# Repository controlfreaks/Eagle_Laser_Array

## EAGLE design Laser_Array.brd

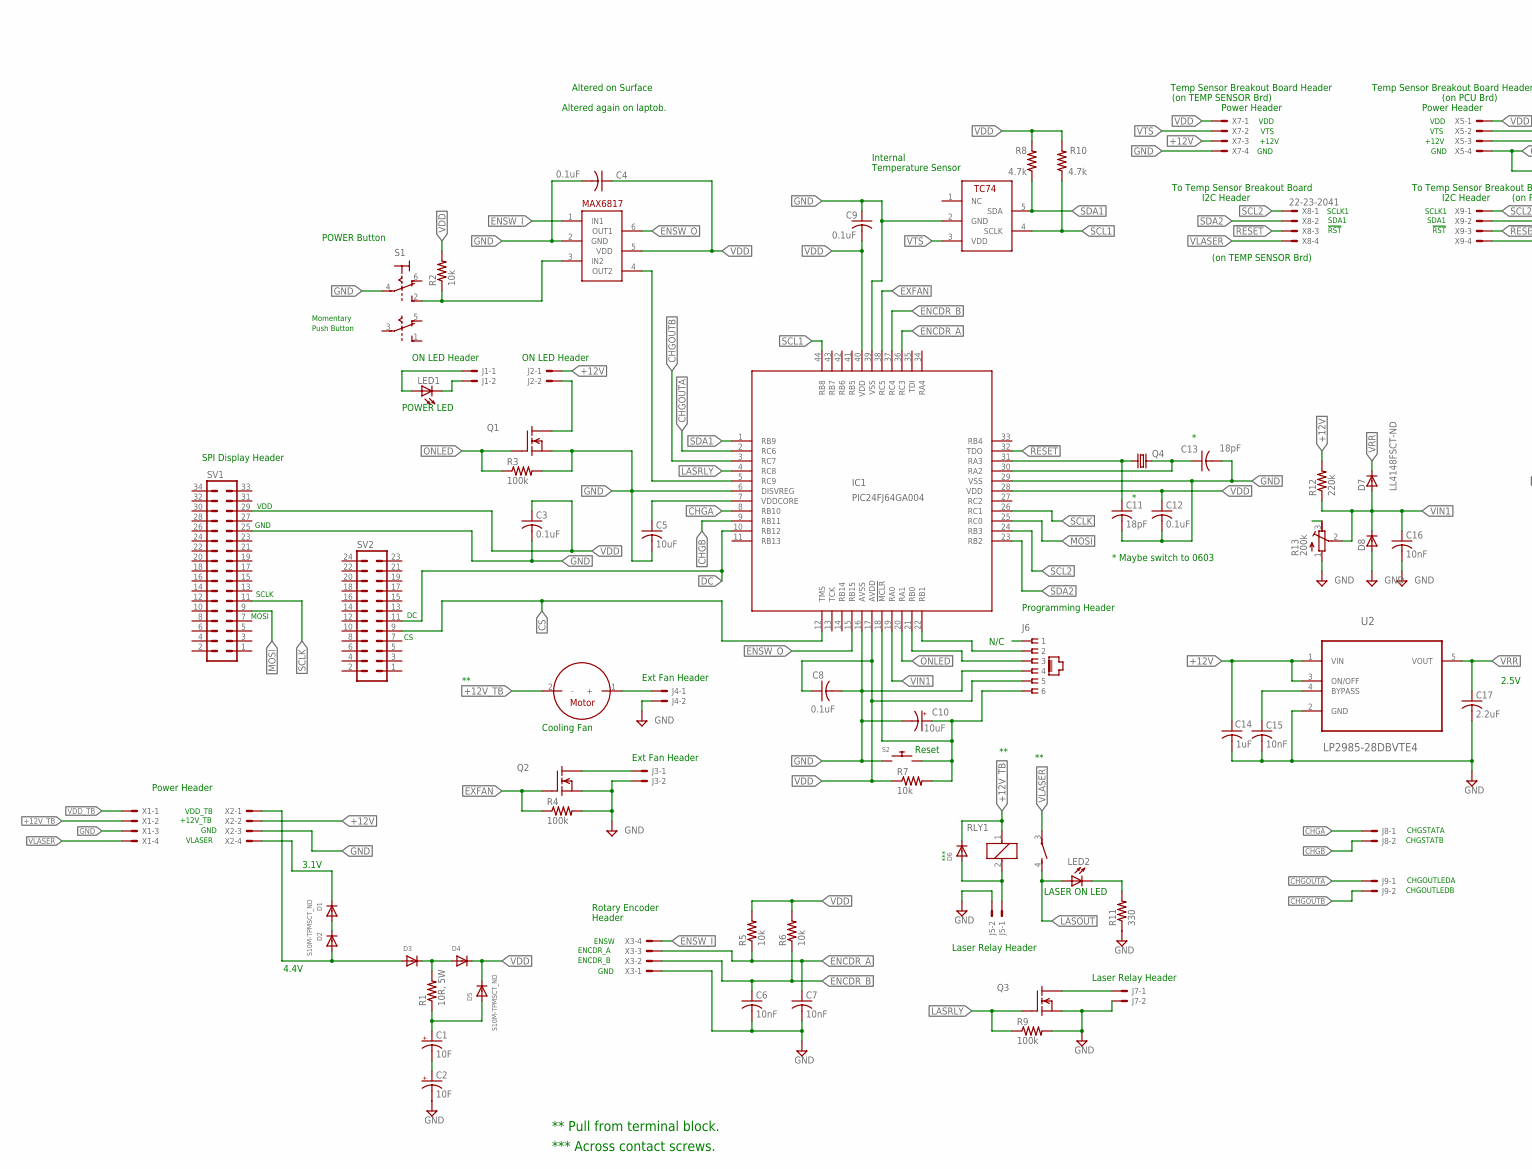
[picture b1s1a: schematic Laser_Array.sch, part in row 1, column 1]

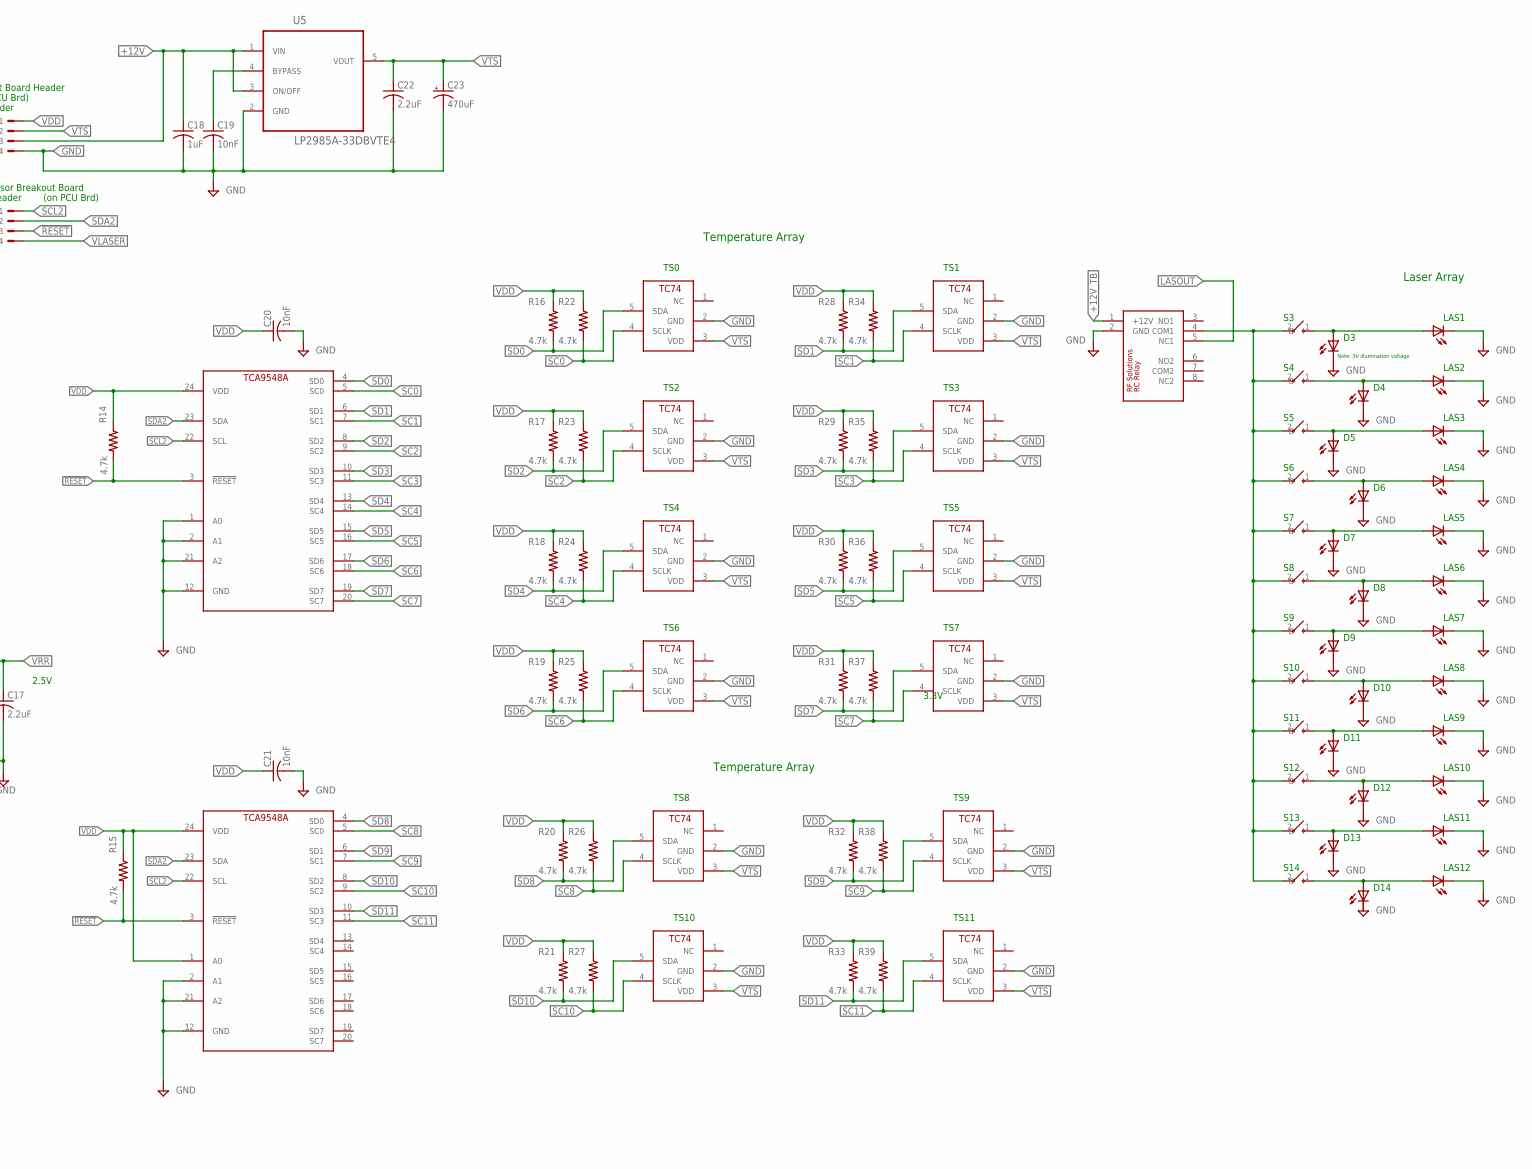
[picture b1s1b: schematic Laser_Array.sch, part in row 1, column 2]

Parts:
C1, C2: 10F; E5-10,5
C3, C4, C8, C9, C12: 0.1uF; C0805
C5: 10uF; C0805
C6, C7, C15, C16, C19, C20, C21: 10nF; C0805
C10: 10uF; CAP3X3
C11, C13: 18pF; C0805
C14, C18: 1uF; C0805
C17, C22: 2.2uF; C0805
C23: 470uF; PANASONIC_F
D1, D5: S10M-TPMSCT_ND; S10M-TPMSCT-ND
D2, D3, D4, D6: 641-1014-6-ND; SOD-123
D7, D8: LL4148FSCT-ND; SOD80
IC1: PIC24FJ64GA004; TQFP44
J1, J2, J3, J4, J5, J7, J8, J9: 22-23-2021
J6: RJ_25; RJ11-NO_SHIELD
LED1, LED2: LEDA5MM; LED5MM
LED3, LED4, LED5, LED6, LED7, LED8, LED9, LED10, LED11, LED12, LED13, LED14, LED15, LED16, LED17, LED18, LED19, LED20, LED21, LED22, LED23, LED24, LED25, LED26: LED3MM
M1: MOTOR; 22-23-2021
Q1, Q2, Q3: QS5U34CT-ND_MOSFET_N_CHANNEL; SOT23-5L
Q4: CRYSTALSM49; SM49
R1: 10R, 5W; RESISTOR5W
R2, R7: 10k; R0805
R3, R4, R9: 100k; R0805
R5, R6: 10k; M0805
R8, R10, R14, R15, R16, R17, R18, R19, R20, R21, R22, R23, R24, R25, R26, R27, R28, R29, R30, R31, R32, R33, R34, R35, R36, R37, R38, R39: 4.7k; M0805
R11: 330; R0805
R12: 220k; M0805
R13: 200k; RTRIM3224X
RLY1: RELAY_SPST
RLY2: RF_SOLUTIONS_RELAY
S1: DPDT_TOGGLE; 22-23-2061
S2: TACT_PB; PUSHBUTTON_SMD_SJ
S3, S4, S5, S6, S7, S8, S9, S10, S11, S12, S13, S14, S15: TC74; SOT23-5L
S16, S17, S18, S19, S20, S21, S22, S23, S24, S25, S26, S27: TOGGLE_SPST; 22-23-2021
SV1: MA17-2W
SV2: MA12-2
U1: MAX6817; SOT23-6
U2: LP2985-28DBVTE4; SOT95P280X145-5N
U3, U4: TCA9548A; TSSOP24
U5: LP2985A-33DBVTE4; SOT95P280X145-5N
X1, X2, X3, X5, X7, X8, X9: 22-23-2041

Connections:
!RESET: IC1.32 (TDO), R14.2, R15.2, U3.3 (!RESET), U4.3 (!RESET), X8.3, X9.3
+12V: C14.1, C18.1, J2.1, R12.2, U2.1 (VIN), U2.3 (ON/OFF), U5.1 (VIN), U5.3 (ON/OFF), X2.2, X5.3, X7.3
+12V_TB: D6.C, M1.2 (-), RLY1.1, RLY2.1 (+12V), X1.2
CHGA: IC1.8 (RB10), J8.1
CHGB: IC1.9 (RB11), J8.2
CHGOUTA: IC1.2 (RC6), J9.1
CHGOUTB: IC1.3 (RC7), J9.2
CS: IC1.12 (TMS), SV2.9
DC: IC1.10 (RB12), SV2.11
ENCDR_A: C7.1, IC1.36 (RC3), R5.1, X3.3
ENCDR_B: C6.1, IC1.37 (RC4), R6.1, X3.2
ENSW_I: U1.1 (IN1), X3.4
ENSW_O: IC1.15 (RB15), U1.6 (OUT1)
EXFAN: IC1.38 (RC5), Q2.1 (G), R4.1
GND: C2.-, C3.2, C4.2, C5.2, C6.2, C7.2, C8.2, C9.1, C10.-, C11.2, C12.2, C13.2, C14.2, C15.2, C16.2, C17.2, C18.2, C19.2, C20.2, C21.2, C22.2, C23.-, D8.2 (A), IC1.6 (DISVREG), IC1.16 (AVSS), IC1.29 (VSS), IC1.39 (VSS), J3.2, J4.2, J5.2, J6.4, J7.2, LED3.K (C), LED4.K (C), LED5.K (C), LED6.K (C), LED7.K (C), LED8.K (C), LED9.K (C), LED10.K (C), LED11.K (C), LED12.K (C), LED13.K (C), LED15.K (C), LED16.K (C), LED17.K (C), LED18.K (C), LED19.K (C), LED20.K (C), LED21.K (C), LED22.K (C), LED23.K (C), LED24.K (C), LED25.K (C), LED26.K (C), Q1.2 (S), Q2.2 (S), Q3.2 (S), R3.2, R4.2, R9.2, R11.1, R13.1 (A), RLY2.2 (GND), S1.4, S2.1, S2.2 (1), S3.2 (GND), S4.2 (GND), S5.2 (GND), S6.2 (GND), S7.2 (GND), S8.2 (GND), S9.2 (GND), S10.2 (GND), S11.2 (GND), S12.2 (GND), S13.2 (GND), S14.2 (GND), S15.2 (GND), SV1.25, U1.2 (GND), U2.2 (GND), U3.1 (A0), U3.2 (A1), U3.12 (GND), U3.21 (A2), U4.2 (A1), U4.12 (GND), U4.21 (A2), U5.2 (GND), X1.3, X2.3, X3.1, X5.4, X7.4
LASOUT: LED2.A, RLY1.4 (S), RLY2.5 (NC1)
LASRLY: IC1.4 (RC8), Q3.1 (G), R9.1
MOSI: IC1.25 (RC0), SV1.9
unnamed: C10.+, IC1.18 (!MCLR), J6.6, R7.2, S2.3 (2), S2.4 (2)
unnamed: C5.1, IC1.7 (VDDCORE)
unnamed: IC1.22 (RB1), J6.2
unnamed: IC1.21 (RB0), J6.3
unnamed: C11.1, IC1.31 (RA3), Q4.1
unnamed: C13.1, IC1.30 (RA2), Q4.2
unnamed: D1.A, D2.C
unnamed: R2.1, S1.2 (S), U1.3 (IN2)
unnamed: IC1.5 (RC9), U1.4 (OUT2)
unnamed: J1.2, LED1.K (C)
unnamed: J3.1, Q2.5 (D)
unnamed: D6.A, J5.1, RLY1.2
unnamed: LED4.A, LED17.A, S18.1 (O)
unnamed: RLY2.4 (COM1), S16.2 (I), S17.2 (I), S18.2 (I), S19.2 (I), S20.2 (I), S21.2 (I), S22.2 (I), S23.2 (I), S24.2 (I), S25.2 (I), S26.2 (I), S27.2 (I)
unnamed: LED3.A, LED15.A, S16.1 (O)
unnamed: LED9.A, LED16.A, S17.1 (O)
unnamed: LED10.A, LED18.A, S19.1 (O)
unnamed: LED5.A, LED19.A, S20.1 (O)
unnamed: LED11.A, LED20.A, S21.1 (O)
unnamed: LED6.A, LED21.A, S22.1 (O)
unnamed: LED12.A, LED22.A, S23.1 (O)
unnamed: LED7.A, LED23.A, S24.1 (O)
unnamed: LED13.A, LED24.A, S25.1 (O)
unnamed: LED8.A, LED25.A, S26.1 (O)
unnamed: LED14.A, LED26.A, S27.1 (O)
unnamed: LED2.K (C), R11.2
unnamed: J1.1, LED1.A
unnamed: C19.1, U5.4 (BYPASS)
unnamed: J2.2, Q1.5 (D)
unnamed: D3.C, D4.A, R1.2
unnamed: J7.1, Q3.5 (D)
unnamed: J4.1, M1.1 (+)
unnamed: C1.-, C2.+
unnamed: C1.+, D5.A, R1.1
unnamed: C15.1, U2.4 (BYPASS)
ONLED: IC1.20 (RA1), Q1.1 (G), R3.1
SC0: R22.2, S4.4 (SCLK), U3.5 (SC0)
SC1: R34.2, S10.4 (SCLK), U3.7 (SC1)
SC2: R23.2, S5.4 (SCLK), U3.9 (SC2)
SC3: R35.2, S11.4 (SCLK), U3.11 (SC3)
SC4: R24.2, S6.4 (SCLK), U3.14 (SC4)
SC5: R36.2, S12.4 (SCLK), U3.16 (SC5)
SC6: R25.2, S7.4 (SCLK), U3.18 (SC6)
SC7: R37.2, S13.4 (SCLK), U3.20 (SC7)
SC8: R26.2, S8.4 (SCLK), U4.5 (SC0)
SC9: R38.2, S14.4 (SCLK), U4.7 (SC1)
SC10: R27.2, S9.4 (SCLK), U4.9 (SC2)
SC11: R39.2, S15.4 (SCLK), U4.11 (SC3)
SCL1: IC1.44 (RB8), R10.1, S3.4 (SCLK)
SCL2: IC1.24 (RB3), U3.22 (SCL), U4.22 (SCL), X8.1, X9.1
SCLK: IC1.26 (RC1), SV1.11
SD0: R16.2, S4.5 (SDA), U3.4 (SD0)
SD1: R28.2, S10.5 (SDA), U3.6 (SD1)
SD2: R17.2, S5.5 (SDA), U3.8 (SD2)
SD3: R29.2, S11.5 (SDA), U3.10 (SD3)
SD4: R18.2, S6.5 (SDA), U3.13 (SD4)
SD5: R30.2, S12.5 (SDA), U3.15 (SD5)
SD6: R19.2, S7.5 (SDA), U3.17 (SD6)
SD7: R31.2, S13.5 (SDA), U3.19 (SD7)
SD8: R20.2, S8.5 (SDA), U4.4 (SD0)
SD9: R32.2, S14.5 (SDA), U4.6 (SD1)
SD10: R21.2, S9.5 (SDA), U4.8 (SD2)
SD11: R33.2, S15.5 (SDA), U4.10 (SD3)
SDA1: IC1.1 (RB9), R8.1, S3.5 (SDA)
SDA2: IC1.23 (RB2), U3.23 (SDA), U4.23 (SDA), X8.2, X9.2
VDD: C3.1, C4.1, C8.1, C9.2, C12.1, C20.1, C21.1, D4.C, D5.C, IC1.17 (AVDD), IC1.28 (VDD), IC1.40 (VDD), J6.5, R2.2, R5.2, R6.2, R7.1, R8.2, R10.2, R14.1, R15.1, R16.1, R17.1, R18.1, R19.1, R20.1, R21.1, R22.1, R23.1, R24.1, R25.1, R26.1, R27.1, R28.1, R29.1, R30.1, R31.1, R32.1, R33.1, R34.1, R35.1, R36.1, R37.1, R38.1, R39.1, SV1.29, U1.5 (VDD), U3.24 (VDD), U4.1 (A0), U4.24 (VDD), X5.1, X7.1
VDD_TB: D2.A, D3.A, X1.1, X2.1
VIN1: C16.1, D7.2 (A), D8.1 (C), IC1.19 (RA0), R12.1, R13.2 (S)
VLASER: D1.C, RLY1.3, X1.4, X2.4, X8.4, X9.4
VRR: C17.1, D7.1 (C), U2.5 (VOUT)
VTS: C22.1, C23.+, S3.3 (VDD), S4.3 (VDD), S5.3 (VDD), S6.3 (VDD), S7.3 (VDD), S8.3 (VDD), S9.3 (VDD), S10.3 (VDD), S11.3 (VDD), S12.3 (VDD), S13.3 (VDD), S14.3 (VDD), S15.3 (VDD), U5.5 (VOUT), X5.2, X7.2

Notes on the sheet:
Power Header
Programming Header
N/C
* Maybe switch to 0603
Reset
SPI Display Header
VDD
GND
SCLK
MOSI
Momentary
Push Button
POWER Button
POWER LED
Cooling Fan
Internal
Temperature Sensor
2.5V
Rotary Encoder
ENSW
ENCDR_A
ENCDR_B
Header
** Pull from terminal block.
CHGSTATA
CHGSTATB
S10
S11
S12
S13
S14
D10
D11
D12
D13
D14
LAS1
LAS2
LAS3
LAS4

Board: 2 copper layers, 154 parts (0 on the bottom side), 89 nets, no tracks yet.

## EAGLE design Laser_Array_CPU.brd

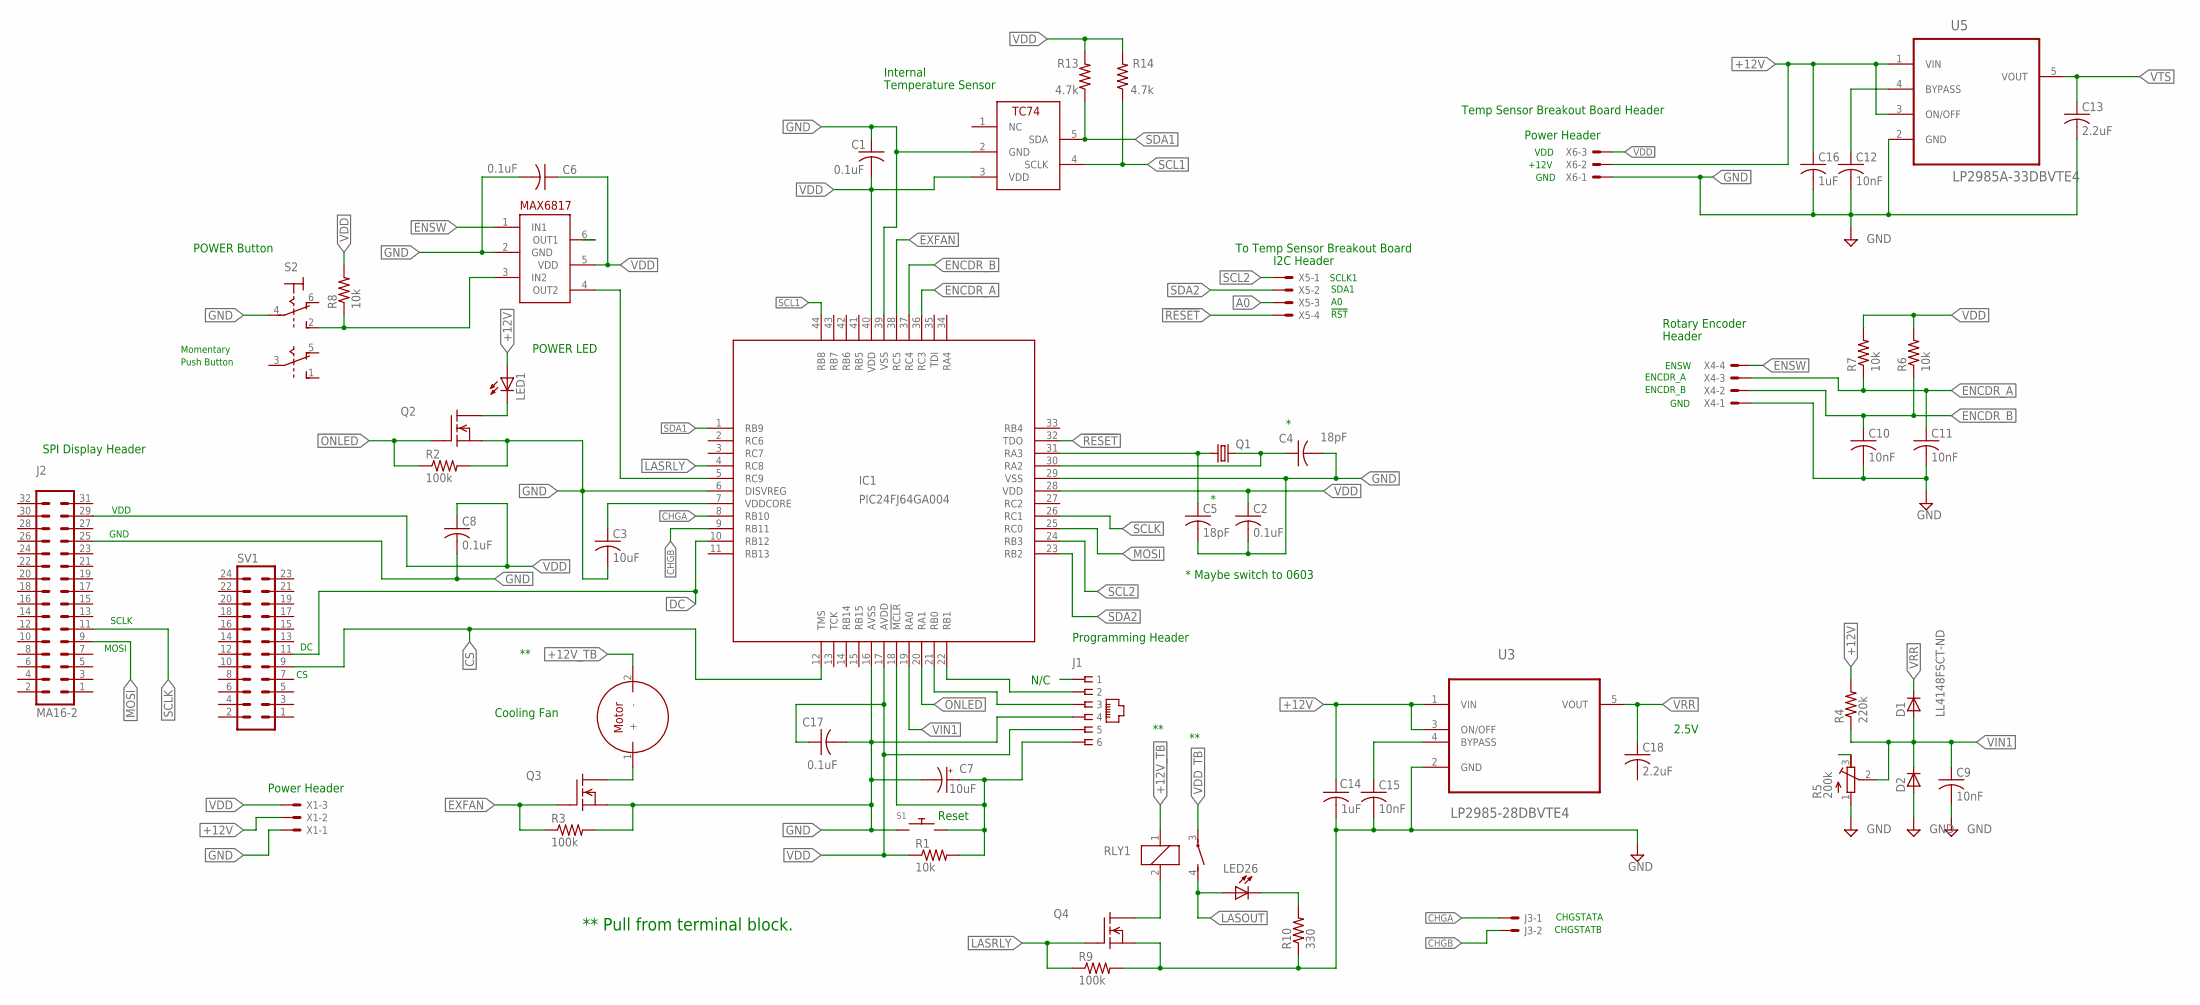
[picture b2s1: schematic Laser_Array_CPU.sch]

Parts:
C1, C2, C6, C8, C17: 0.1uF; C0805
C3: 10uF; C0805
C4, C5: 18pF; C0805
C7: 10uF; CAP3X3
C9, C10, C11, C12, C15: 10nF; C0805
C13, C18: 2.2uF; C0805
C14, C16: 1uF; C0805
D1, D2: LL4148FSCT-ND; SOD80
IC1: PIC24FJ64GA004; TQFP44
J1: RJ_25; RJ11-NO_SHIELD
J2: MA16-2
J3: 22-23-2021
LED1, LED26: LEDA5MM; LED5MM
M1: MOTOR; 22-23-2021
Q1: CRYSTALSM49; SM49
Q2, Q3, Q4: QS5U34CT-ND_MOSFET_N_CHANNEL; SOT23-5L
R1, R8: 10k; R0805
R2, R3, R9: 100k; R0805
R4: 220k; M0805
R5: 200k; RTRIM3224X
R6, R7: 10k; M0805
R10: 330; R0805
R13, R14: 4.7k; M0805
RLY1: RELAY_SPST
S1: TACT_PB; PUSHBUTTON_SMD_SJ
S2: DPDT_TOGGLE; 22-23-2061
S3: TC74; SOT23-5L
SV1: MA12-2
U2: MAX6817; SOT23-6
U3: LP2985-28DBVTE4; SOT95P280X145-5N
U5: LP2985A-33DBVTE4; SOT95P280X145-5N
X1, X6: 22-23-2031
X4, X5: 22-23-2041

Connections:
!RESET: IC1.32 (TDO), X5.4
+12V: C14.1, C16.1, LED1.A, R4.2, U3.1 (VIN), U3.3 (ON/OFF), U5.1 (VIN), U5.3 (ON/OFF), X1.2, X6.2
+12V_TB: M1.2 (-), RLY1.1
A0: X5.3
CHGA: IC1.8 (RB10), J3.1
CHGB: IC1.9 (RB11), J3.2
CS: IC1.12 (TMS), SV1.9
DC: IC1.10 (RB12), SV1.11
ENCDR_A: C11.1, IC1.36 (RC3), R7.1, X4.3
ENCDR_B: C10.1, IC1.37 (RC4), R6.1, X4.2
ENSW: U2.1 (IN1), X4.4
EXFAN: IC1.38 (RC5), Q3.1 (G), R3.1
GND: C1.1, C2.2, C3.2, C4.2, C5.2, C6.2, C7.-, C8.2, C9.2, C10.2, C11.2, C12.2, C13.2, C14.2, C15.2, C16.2, C17.2, D2.2 (A), IC1.6 (DISVREG), IC1.16 (AVSS), IC1.29 (VSS), IC1.39 (VSS), J1.4, J2.25, Q2.2 (S), Q3.2 (S), Q4.2 (S), R2.2, R3.2, R5.1 (A), R9.2, R10.1, S1.1, S1.2 (1), S2.4, S3.2 (GND), U2.2 (GND), U3.2 (GND), U5.2 (GND), X1.1, X4.1, X6.1
LASOUT: LED26.A, RLY1.4 (S)
LASRLY: IC1.4 (RC8), Q4.1 (G), R9.1
MOSI: IC1.25 (RC0), J2.9
unnamed: C7.+, IC1.18 (!MCLR), J1.6, R1.2, S1.3 (2), S1.4 (2)
unnamed: C3.1, IC1.7 (VDDCORE)
unnamed: IC1.22 (RB1), J1.2
unnamed: IC1.21 (RB0), J1.3
unnamed: C5.1, IC1.31 (RA3), Q1.1
unnamed: C4.1, IC1.30 (RA2), Q1.2
unnamed: R8.1, S2.2 (S), U2.3 (IN2)
unnamed: IC1.5 (RC9), U2.4 (OUT2)
unnamed: LED1.K (C), Q2.5 (D)
unnamed: M1.1 (+), Q3.5 (D)
unnamed: Q4.5 (D), RLY1.2
unnamed: LED26.K (C), R10.2
unnamed: C12.1, U5.4 (BYPASS)
unnamed: C15.1, U3.4 (BYPASS)
ONLED: IC1.20 (RA1), Q2.1 (G), R2.1
SCL1: IC1.44 (RB8), R14.1, S3.4 (SCLK)
SCL2: IC1.24 (RB3), X5.1
SCLK: IC1.26 (RC1), J2.11
SDA1: IC1.1 (RB9), R13.1, S3.5 (SDA)
SDA2: IC1.23 (RB2), X5.2
VDD: C1.2, C2.1, C6.1, C8.1, C17.1, IC1.17 (AVDD), IC1.28 (VDD), IC1.40 (VDD), J1.5, J2.29, R1.1, R6.2, R7.2, R8.2, R13.2, R14.2, S3.3 (VDD), U2.5 (VDD), X1.3, X6.3
VDD_TB: RLY1.3
VIN1: C9.1, D1.2 (A), D2.1 (C), IC1.19 (RA0), R4.1, R5.2 (S)
VRR: C18.1, D1.1 (C), U3.5 (VOUT)
VTS: C13.1, U5.5 (VOUT)

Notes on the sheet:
Power Header
Programming Header
N/C
* Maybe switch to 0603
Reset
SPI Display Header
VDD
GND
SCLK
MOSI
Momentary
Push Button
POWER Button
POWER LED
Cooling Fan
Internal
Temperature Sensor
2.5V
Rotary Encoder
ENSW
ENCDR_A
ENCDR_B
Header
** Pull from terminal block.
CHGSTATA
CHGSTATB
I2C Header
SCLK1
SDA1
!RST
+12V
Temp Sensor Breakout Board Header
To Temp Sensor Breakout Board

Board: 2 copper layers, 55 parts (0 on the bottom side), 39 nets, no tracks yet.

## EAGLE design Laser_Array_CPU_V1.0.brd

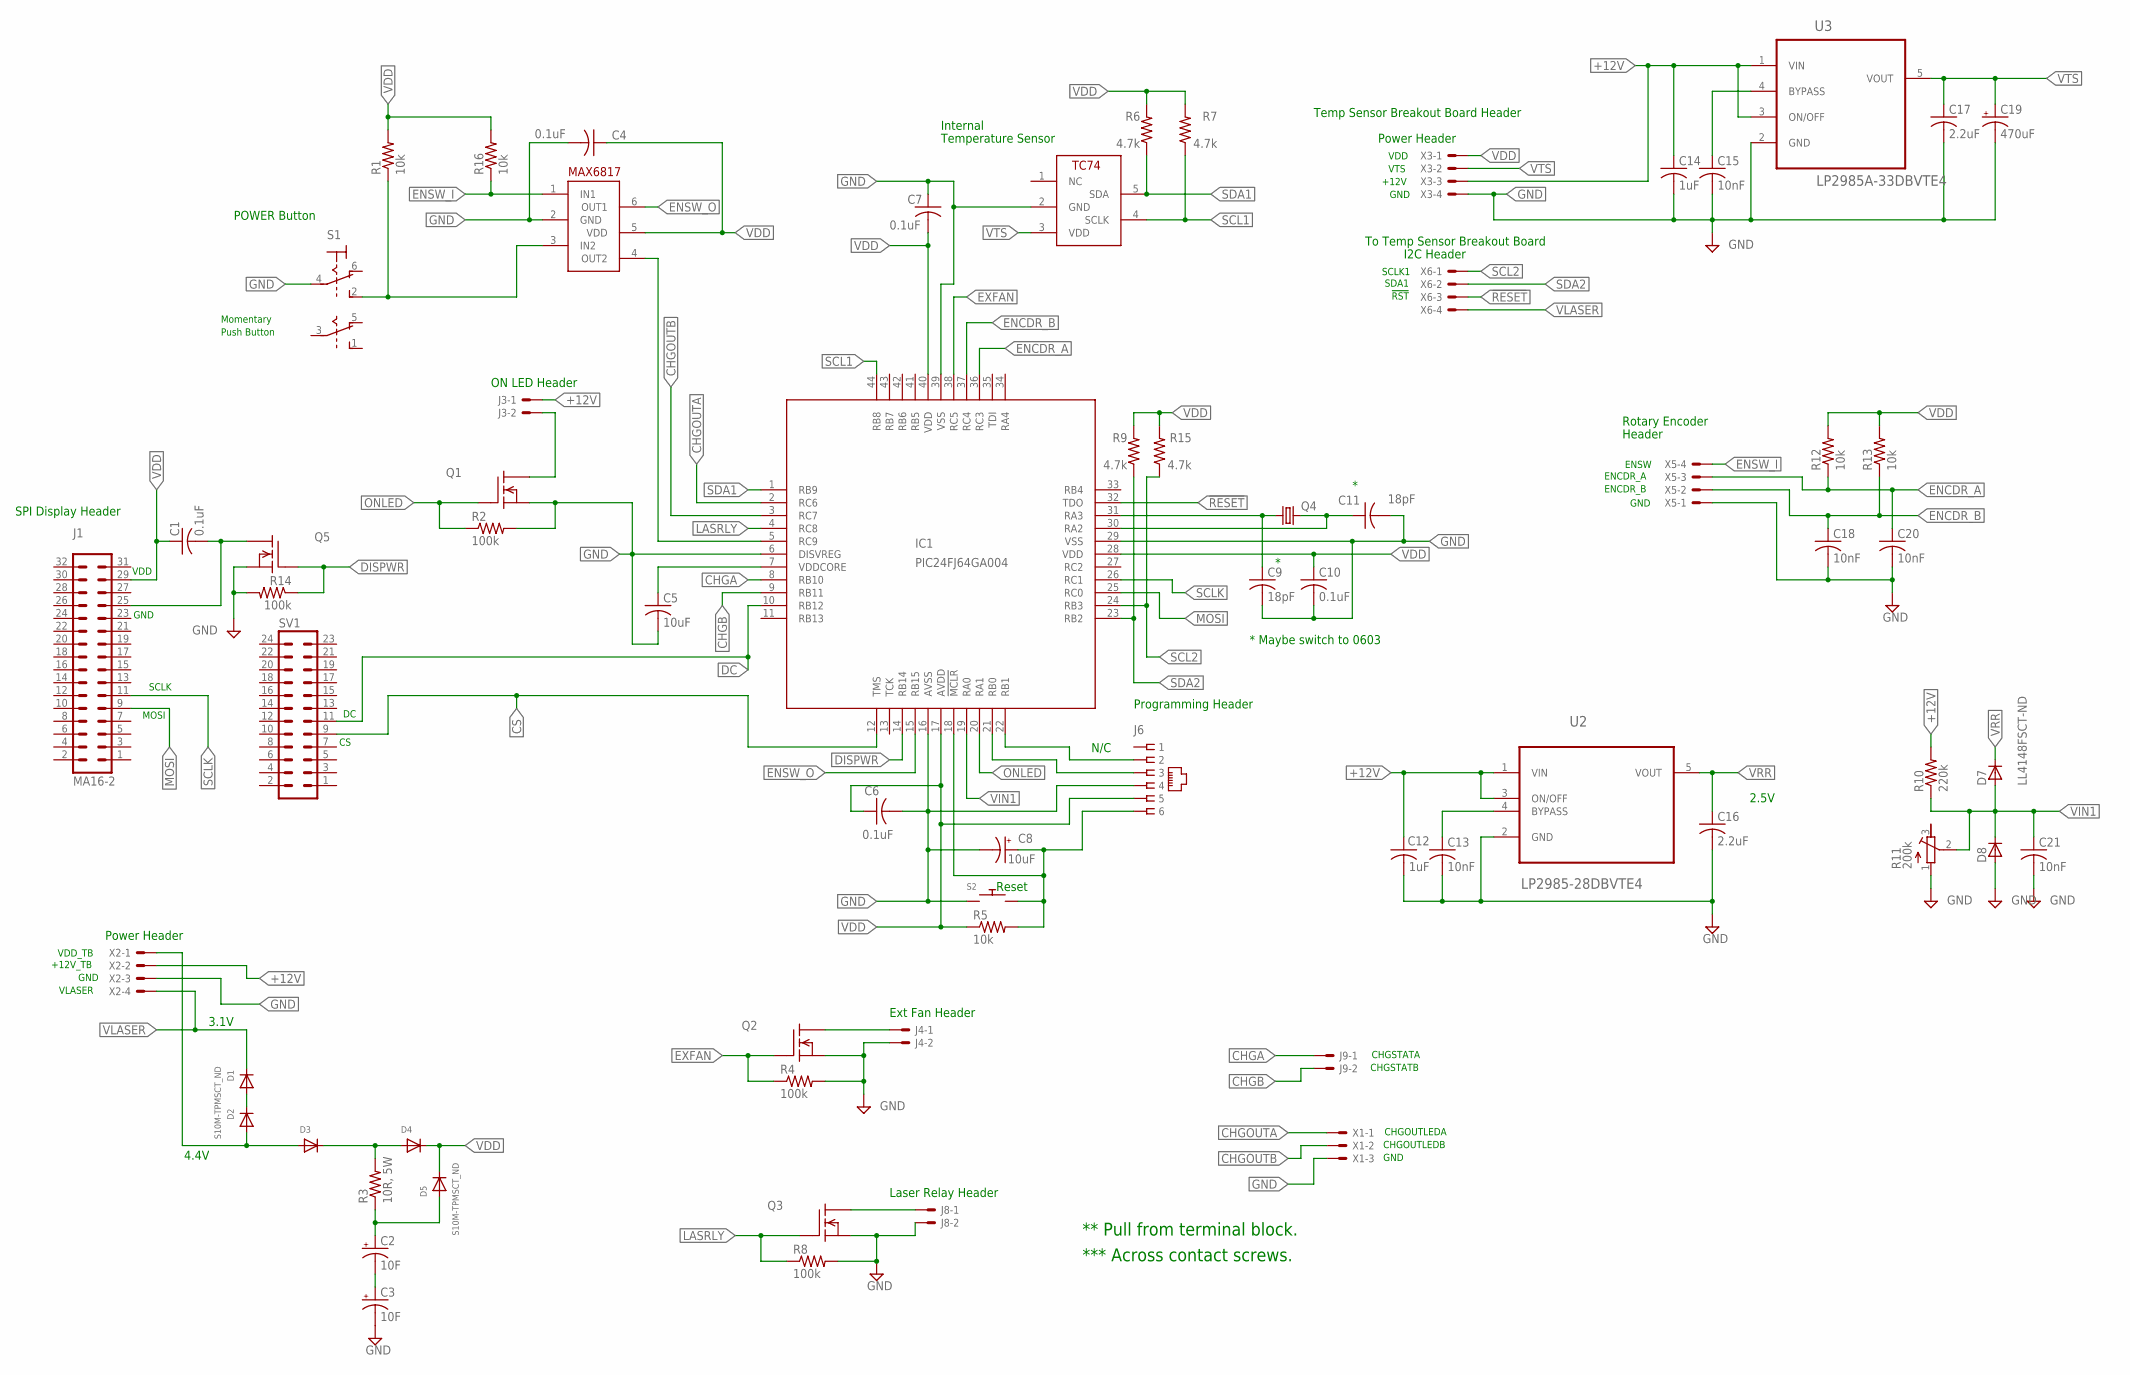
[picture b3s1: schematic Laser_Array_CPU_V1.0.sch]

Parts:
C1, C4, C6, C7, C10: 0.1uF; C0805
C2, C3: 10F; E5-10,5
C5: 10uF; C0805
C8: 10uF; CAP3X3
C9, C11: 18pF; C0805
C12, C14: 1uF; C0805
C13, C15, C18, C20, C21: 10nF; C0805
C16, C17: 2.2uF; C0805
C19: 470uF; PANASONIC_F
D1, D5: S10M-TPMSCT_ND; S10M-TPMSCT-ND
D2, D3, D4: 641-1014-6-ND; SOD-123
D7, D8: LL4148FSCT-ND; SOD80
IC1: PIC24FJ64GA004; TQFP44
J1: MA16-2
J3, J4, J8, J9: 22-23-2021
J6: RJ_25; RJ11-NO_SHIELD
Q1, Q2, Q3, Q5: QS5U34CT-ND_MOSFET_N_CHANNEL; SOT23-5L
Q4: CRYSTALSM49; SM49
R1, R5, R16: 10k; R0805
R2, R4, R8, R14: 100k; R0805
R3: 10R, 5W; RESISTOR5W
R6, R7, R9, R15: 4.7k; M0805
R10: 220k; M0805
R11: 200k; RTRIM3224X
R12, R13: 10k; M0805
S1: DPDT_TOGGLE; 22-23-2061
S2: TACT_PB; PUSHBUTTON_SMD_SJ
S3: TC74; SOT23-5L
SV1: MA12-2
U1: MAX6817; SOT23-6
U2: LP2985-28DBVTE4; SOT95P280X145-5N
U3: LP2985A-33DBVTE4; SOT95P280X145-5N
X1: 22-23-2031
X2, X3, X5, X6: 22-23-2041

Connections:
!RESET: IC1.32 (TDO), X6.3
+12V: C12.1, C14.1, J3.1, R10.2, U2.1 (VIN), U2.3 (ON/OFF), U3.1 (VIN), U3.3 (ON/OFF), X2.2, X3.3
CHGA: IC1.8 (RB10), J9.1
CHGB: IC1.9 (RB11), J9.2
CHGOUTA: IC1.2 (RC6), X1.1
CHGOUTB: IC1.3 (RC7), X1.2
CS: IC1.12 (TMS), SV1.9
DC: IC1.10 (RB12), SV1.11
DISPWR: IC1.14 (RB14), Q5.1 (G), R14.1
ENCDR_A: C20.1, IC1.36 (RC3), R12.1, X5.3
ENCDR_B: C18.1, IC1.37 (RC4), R13.1, X5.2
ENSW_I: R16.1, U1.1 (IN1), X5.4
ENSW_O: IC1.15 (RB15), U1.6 (OUT1)
EXFAN: IC1.38 (RC5), Q2.1 (G), R4.1
GND: C3.-, C4.2, C5.2, C6.2, C7.1, C8.-, C9.2, C10.2, C11.2, C12.2, C13.2, C14.2, C15.2, C16.2, C17.2, C18.2, C19.-, C20.2, C21.2, D8.2 (A), IC1.6 (DISVREG), IC1.16 (AVSS), IC1.29 (VSS), IC1.39 (VSS), J4.2, J6.4, J8.2, Q1.2 (S), Q2.2 (S), Q3.2 (S), Q5.2 (S), R2.2, R4.2, R8.2, R11.1 (A), R14.2, S1.4, S2.1, S2.2 (1), S3.2 (GND), U1.2 (GND), U2.2 (GND), U3.2 (GND), X1.3, X2.3, X3.4, X5.1
LASRLY: IC1.4 (RC8), Q3.1 (G), R8.1
MOSI: IC1.25 (RC0), J1.9
unnamed: C8.+, IC1.18 (!MCLR), J6.6, R5.2, S2.3 (2), S2.4 (2)
unnamed: C5.1, IC1.7 (VDDCORE)
unnamed: IC1.22 (RB1), J6.2
unnamed: IC1.21 (RB0), J6.3
unnamed: C9.1, IC1.31 (RA3), Q4.1
unnamed: C11.1, IC1.30 (RA2), Q4.2
unnamed: C1.2, J1.25, Q5.5 (D)
unnamed: R1.1, S1.2 (S), U1.3 (IN2)
unnamed: IC1.5 (RC9), U1.4 (OUT2)
unnamed: J3.2, Q1.5 (D)
unnamed: D1.A, D2.C
unnamed: J4.1, Q2.5 (D)
unnamed: D3.C, D4.A, R3.2
unnamed: J8.1, Q3.5 (D)
unnamed: C15.1, U3.4 (BYPASS)
unnamed: C2.-, C3.+
unnamed: C2.+, D5.A, R3.1
unnamed: C13.1, U2.4 (BYPASS)
ONLED: IC1.20 (RA1), Q1.1 (G), R2.1
SCL1: IC1.44 (RB8), R7.1, S3.4 (SCLK)
SCL2: IC1.24 (RB3), R15.1, X6.1
SCLK: IC1.26 (RC1), J1.11
SDA1: IC1.1 (RB9), R6.1, S3.5 (SDA)
SDA2: IC1.23 (RB2), R9.1, X6.2
VDD: C1.1, C4.1, C6.1, C7.2, C10.1, D4.C, D5.C, IC1.17 (AVDD), IC1.28 (VDD), IC1.40 (VDD), J1.29, J6.5, R1.2, R5.1, R6.2, R7.2, R9.2, R12.2, R13.2, R15.2, R16.2, U1.5 (VDD), X3.1
VDD_TB: D2.A, D3.A, X2.1
VIN1: C21.1, D7.2 (A), D8.1 (C), IC1.19 (RA0), R10.1, R11.2 (S)
VLASER: D1.C, X2.4, X6.4
VRR: C16.1, D7.1 (C), U2.5 (VOUT)
VTS: C17.1, C19.+, S3.3 (VDD), U3.5 (VOUT), X3.2

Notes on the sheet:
Programming Header
N/C
* Maybe switch to 0603
Reset
SPI Display Header
VDD
GND
SCLK
MOSI
Momentary
Push Button
POWER Button
Internal
Temperature Sensor
2.5V
Rotary Encoder
ENSW
ENCDR_A
ENCDR_B
Header
CHGSTATA
CHGSTATB
I2C Header
SCLK1
SDA1
!RST
Power Header
+12V
Temp Sensor Breakout Board Header
To Temp Sensor Breakout Board
CHGOUTLEDA
CHGOUTLEDB
ON LED Header
VTS
Laser Relay Header
** Pull from terminal block.
4.4V
3.1V
VDD_TB
+12V_TB

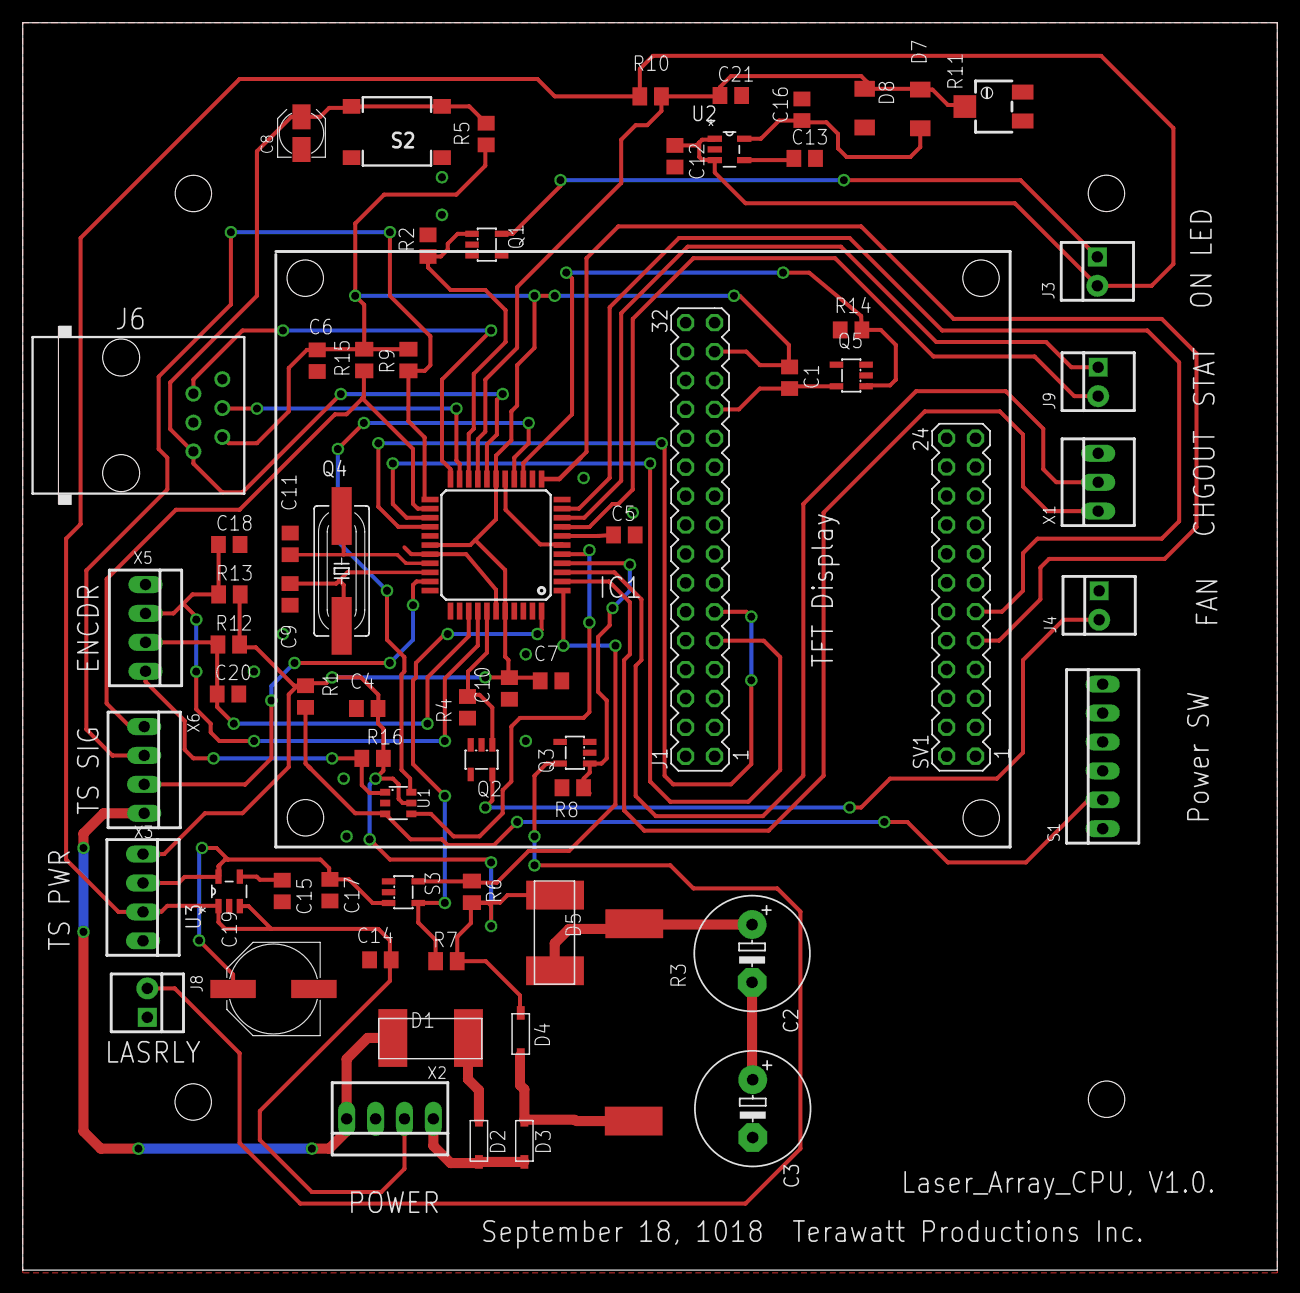
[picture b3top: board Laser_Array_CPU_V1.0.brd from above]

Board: 2 copper layers, 110.2 x 109.6 mm, 68 parts (0 on the bottom side), 47 nets.

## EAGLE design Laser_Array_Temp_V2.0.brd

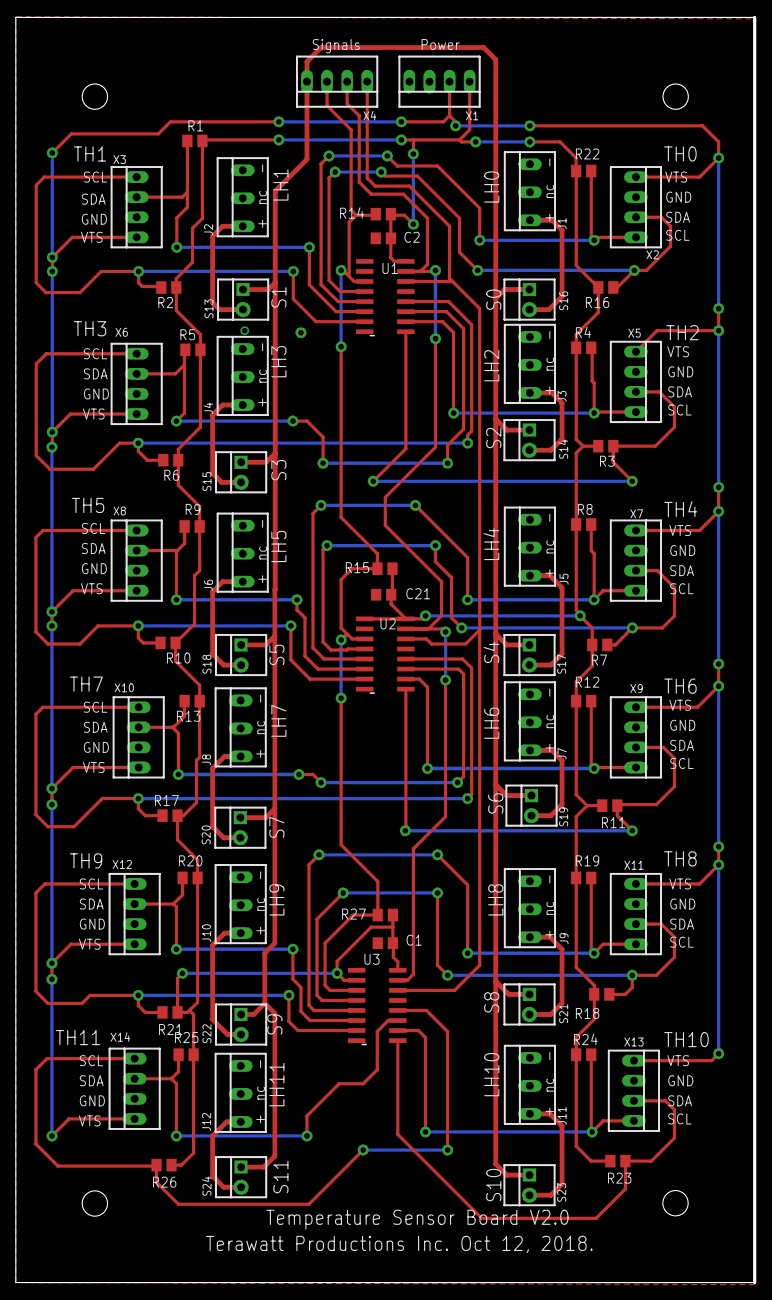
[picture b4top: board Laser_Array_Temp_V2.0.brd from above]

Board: 2 copper layers, 93.5 x 160.0 mm, 71 parts (0 on the bottom side), 43 nets.

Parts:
C1, C2, C21: 10nF; C0805
J1, J2, J3, J4, J5, J6, J7, J8, J9, J10, J11, J12: LASER_MOD
R1, R2, R3, R4, R5, R6, R7, R8, R9, R10, R11, R12, R13, R14, R15, R16, R17, R18, R19, R20, R21, R22, R23, R24, R25, R26, R27: 4.7k; M0805
S13, S14, S15, S16, S17, S18, S19, S20, S21, S22, S23, S24: TOGGLE_SPST; 22-23-2021
U1, U2, U3: TCA9546A; SOIC16N
X1, X2, X3, X4, X5, X6, X7, X8, X9, X10, X11, X12, X13, X14: 22-23-2041

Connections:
!RESET: R14.2, R15.2, R27.2, U1.3, U2.3, U3.3, X4.3
GND: C1.2, C2.2, C21.2, J1.3, J2.3, J3.3, J4.3, J5.3, J6.3, J7.3, J8.3, J9.3, J10.3, J11.3, J12.3, U1.1, U1.2, U1.8, U1.13, U2.2, U2.8, U2.13, U3.1, U3.8, U3.13, X1.4, X2.2, X3.2, X5.2, X6.2, X7.2, X8.2, X9.2, X10.2, X11.2, X12.2, X13.2, X14.2
unnamed: J2.1, S13.1
unnamed: J1.1, S16.1
unnamed: J3.1, S14.1
unnamed: J4.1, S15.1
unnamed: J5.1, S17.1
unnamed: J6.1, S18.1
unnamed: J7.1, S19.1
unnamed: J8.1, S20.1
unnamed: J9.1, S21.1
unnamed: J10.1, S22.1
unnamed: J11.1, S23.1
unnamed: J12.1, S24.1
SC0: R22.2, U1.5, X2.4
SC1: R2.2, U1.7, X3.4
SC2: R4.2, U1.10, X5.4
SC3: R6.2, U1.12, X6.4
SC4: R8.2, U2.5, X7.4
SC5: R10.2, U2.7, X8.4
SC6: R12.2, U2.10, X9.4
SC7: R17.2, U2.12, X10.4
SC8: R19.2, U3.5, X11.4
SC9: R21.2, U3.7, X12.4
SC10: R24.2, U3.10, X13.4
SC11: R26.2, U3.12, X14.4
SCL2: U1.14, U2.14, U3.14, X4.1
SD0: R16.2, U1.4, X2.3
SD1: R1.2, U1.6, X3.3
SD2: R3.2, U1.9, X5.3
SD3: R5.2, U1.11, X6.3
SD4: R7.2, U2.4, X7.3
SD5: R9.2, U2.6, X8.3
SD6: R11.2, U2.9, X9.3
SD7: R13.2, U2.11, X10.3
SD8: R18.2, U3.4, X11.3
SD9: R20.2, U3.6, X12.3
SD10: R23.2, U3.9, X13.3
SD11: R25.2, U3.11, X14.3
SDA2: U1.15, U2.15, U3.15, X4.2
VDD: C1.1, C2.1, C21.1, R1.1, R2.1, R3.1, R4.1, R5.1, R6.1, R7.1, R8.1, R9.1, R10.1, R11.1, R12.1, R13.1, R14.1, R15.1, R16.1, R17.1, R18.1, R19.1, R20.1, R21.1, R22.1, R23.1, R24.1, R25.1, R26.1, R27.1, U1.16, U2.1, U2.16, U3.2, U3.16, X1.1
VLASER: S13.2, S14.2, S15.2, S16.2, S17.2, S18.2, S19.2, S20.2, S21.2, S22.2, S23.2, S24.2, X4.4
VTS: X1.2, X2.1, X3.1, X5.1, X6.1, X7.1, X8.1, X9.1, X10.1, X11.1, X12.1, X13.1, X14.1

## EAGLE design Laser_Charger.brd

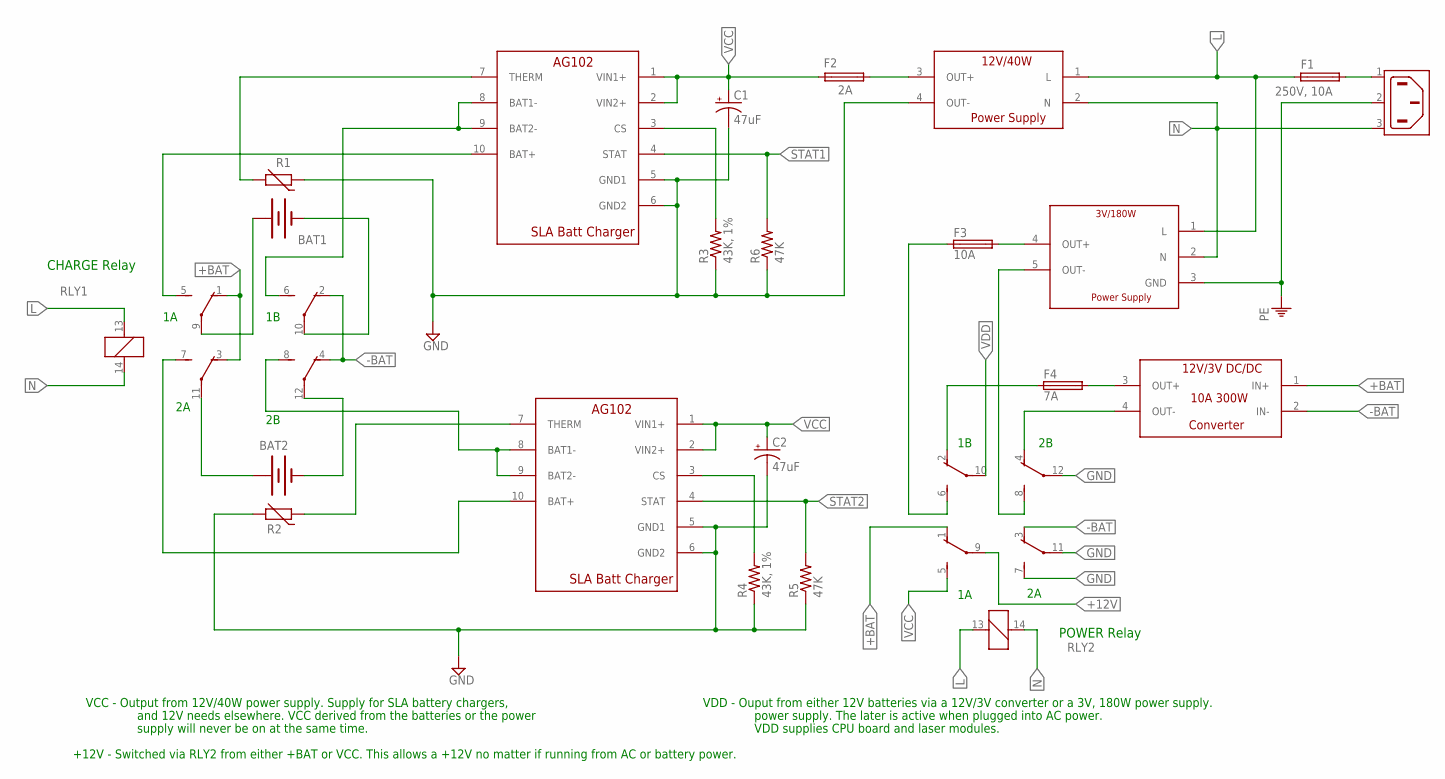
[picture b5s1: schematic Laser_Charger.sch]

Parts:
BAT1, BAT2: BATTERY; 12V_BATT
C1, C2: 47uF; E5-10,5
CHG1, CHG2: AG102_SLA_CHARGER; 22-23-2101
F1: 250V, 10A; SH22,5
F2: 2A; SH22,5
F3: 10A; SH22,5
F4: 7A; SH22,5
P1: 12V/3V_DC/DC_CONVERTER
PS1: 12V/40W_POWER_SUPPLY
PS2: 3V/180W_POWER_SUPPLY
R1, R2: THERMISTOR-2,5; RS-2,5
R3, R4: 43K, 1%; R0805
R5, R6: 47K; R0805
RLY1, RLY2: 4P4T_RELAYS; 22-23-2071-2
X1: 6ESRM-P

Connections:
+12V: RLY2.9
+BAT: P1.1 (IN+), RLY1.1 (O), RLY1.3 (O), RLY2.1 (O)
-BAT: P1.2 (IN-), RLY1.2 (O), RLY1.4 (O), RLY2.3 (O)
GND: C1.-, C2.-, CHG1.5 (GND1), CHG1.6 (GND2), CHG2.5 (GND1), CHG2.6 (GND2), PS1.4 (OUT-), R1.1, R2.2, R3.1, R4.1, R5.1, R6.1, RLY2.7 (S), RLY2.11, RLY2.12
L: F1.1, PS1.1 (L), PS2.1 (L), RLY1.13 (1), RLY2.13 (1)
N: PS1.2 (N), PS2.2 (N), RLY1.14 (2), RLY2.14 (2), X1.3 (AC2)
unnamed: P1.4 (OUT-), RLY2.4 (O)
unnamed: F3.1, RLY2.6 (S)
unnamed: BAT1.1 (+), RLY1.9
unnamed: BAT1.2 (-), RLY1.10
unnamed: BAT2.1 (+), RLY1.11
unnamed: CHG1.8 (BAT1-), CHG1.9 (BAT2-), RLY1.6 (S)
unnamed: CHG1.3 (CS), R3.2
unnamed: BAT2.2 (-), RLY1.12
unnamed: F4.1, RLY2.2 (O)
unnamed: PS2.5 (OUT-), RLY2.8 (S)
unnamed: CHG1.10 (BAT+), RLY1.5 (S)
unnamed: CHG1.7 (THERM), R1.2
unnamed: CHG2.3 (CS), R4.2
unnamed: CHG2.7 (THERM), R2.1
unnamed: CHG2.8 (BAT1-), CHG2.9 (BAT2-), RLY1.8 (S)
unnamed: F1.2, X1.1 (AC1)
unnamed: CHG2.10 (BAT+), RLY1.7 (S)
unnamed: F2.2, PS1.3 (OUT+)
unnamed: F3.2, PS2.4 (OUT+)
unnamed: F4.2, P1.3 (OUT+)
PE: PS2.3 (GND), X1.2 (SH)
STAT1: CHG1.4 (STAT), R6.2
STAT2: CHG2.4 (STAT), R5.2
VCC: C1.+, C2.+, CHG1.1 (VIN1+), CHG1.2 (VIN2+), CHG2.1 (VIN1+), CHG2.2 (VIN2+), F2.1, RLY2.5 (S)
VDD: RLY2.10

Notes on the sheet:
VCC - Output from 12V/40W power supply. Supply for SLA battery chargers,
VDD - Ouput from either 12V batteries via a 12V/3V converter or a 3V, 180W power supply.
power supply. The later is active when plugged into AC power.
VDD supplies CPU board and laser modules.
and 12V needs elsewhere. VCC derived from the batteries or the power
supply will never be on at the same time.
+12V - Switched via RLY2 from either +BAT or VCC. This allows a +12V no matter if running from AC or battery power.
CHARGE Relay
POWER Relay

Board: 2 copper layers, 22 parts (0 on the bottom side), 29 nets, no tracks yet.
